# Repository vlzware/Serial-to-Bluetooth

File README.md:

# RS485 to Bluetooth Hardware Interface

- Connect a RS485 serial interface to a Bluetooth device (like a smartphone);
- Fully programmable function thanks to an ATMEGA microcontroller, easily accessible through 6-pin header;
- Industrial-grade components with lot of redundancy;
- Originally developed as the hardware companion for my [BTDisplay - controlling a Siemens wind turbine with my smartphone](https://github.com/holodon/BTDisplayOSS);
- General purpose LED;
- Rechargeable battery with a simple but effective charging circuit;
- Really small form factor - pictures available in the [media section](media).

## Legal
- Open-source hardware, released under [MIT](LICENSE) license;
- Layout and schematics build with [EAGLE CAD](https://www.autodesk.com/products/eagle/overview).

## 
<p style="text-align: right">
    <a href="https://vlzware.com">Vladimir Zhelezarov</a> © 2017
</p>

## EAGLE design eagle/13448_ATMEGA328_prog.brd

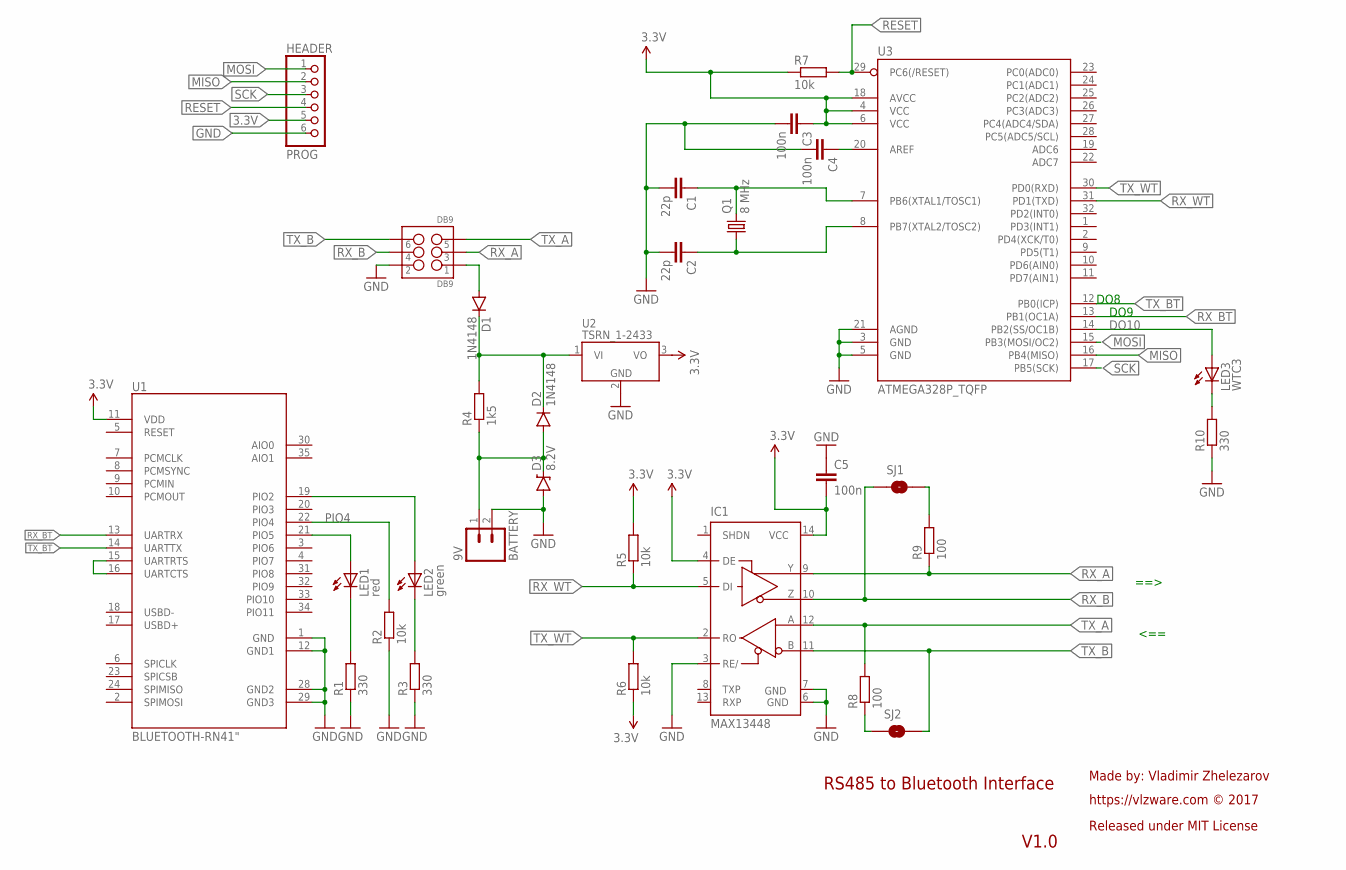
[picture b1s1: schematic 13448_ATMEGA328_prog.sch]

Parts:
BATTERY: 9V; 1X02_LOCK
C1, C2: 22p; 1206
C3, C4, C5: 100n; 1206
D1, D2: 1N4148; DIODE-1N4148
D3: 8.2V; DIODE-BZT52
DB9: DB9; 2X3
HEADER: PROG; 1X06
IC1: MAX13448; SO14
LED1: red; LED3MM
LED2: green; LED3MM
LED3: WTC3; LED3MM
Q1: 8 MHz; HC49UP
R1, R3, R10: 330; M1206
R2, R5, R6, R7: 10k; M1206
R4: 1k5; 0204V
R8, R9: 100; M1206
SJ1, SJ2: SOLDERJUMPERNC; SJ_2S
U1: BLUETOOTH-RN41"; RN41
U2: TSRN_1-2433; TSR-1
U3: ATMEGA328P_TQFP; TQFP32-08

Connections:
3.3V: C3.1, C5.2, HEADER.5, IC1.4 (DE), IC1.14 (VCC), R5.2, R6.1, R7.1, U1.11 (VDD), U2.3 (VO), U3.4 (VCC), U3.6 (VCC), U3.18 (AVCC)
24V: D1.A, DB9.1
D1: LED1.K (C), R1.2
D2: LED2.K (C), R3.2
DO10: LED3.A, U3.14 (PB2(SS/OC1B))
GND: BATTERY.2, C1.2, C2.2, C3.2, C4.2, C5.1, D3.A, DB9.2, HEADER.6, IC1.3 (RE/), IC1.6 (GND), IC1.7 (GND), R1.1, R2.1, R3.1, R10.1, U1.1 (GND), U1.12 (GND1), U1.28 (GND2), U1.29 (GND3), U2.2 (GND), U3.3 (GND), U3.5 (GND), U3.21 (AGND)
MISO: HEADER.2, U3.16 (PB4(MISO))
MOSI: HEADER.1, U3.15 (PB3(MOSI/OC2))
unnamed: LED1.A, U1.21 (PIO5)
unnamed: LED2.A, U1.19 (PIO2)
unnamed: U1.15 (UARTRTS), U1.16 (UARTCTS)
unnamed: LED3.K (C), R10.2
unnamed: R8.1, SJ2.1
unnamed: R9.2, SJ1.2
unnamed: BATTERY.1, D2.A, D3.C, R4.1
unnamed: C4.1, U3.20 (AREF)
unnamed: C1.1, Q1.2, U3.7 (PB6(XTAL1/TOSC1))
unnamed: C2.1, Q1.1, U3.8 (PB7(XTAL2/TOSC2))
PIO4: R2.2, U1.22 (PIO4)
RESET: HEADER.4, R7.2, U3.29 (PC6(/RESET))
RX_A: DB9.3, IC1.9 (Y), R9.1
RX_B: DB9.4, IC1.10 (Z), SJ1.1
RX_BT: U1.13 (UARTRX), U3.13 (PB1(OC1A))
RX_WT: IC1.5 (DI), R5.1, U3.31 (PD1(TXD))
SCK: HEADER.3, U3.17 (PB5(SCK))
TX_A: DB9.5, IC1.12 (A), R8.2
TX_B: DB9.6, IC1.11 (B), SJ2.2
TX_BT: U1.14 (UARTTX), U3.12 (PB0(ICP))
TX_WT: IC1.2 (RO), R6.2, U3.30 (PD0(RXD))
VI: D1.C, D2.C, R4.2, U2.1 (VI)

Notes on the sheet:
==>
<==
DO8
DO9
RS485 to Bluetooth Interface
Made by: Vladimir Zhelezarov
Released under MIT License
https://vlzware.com © 2017
V1.0

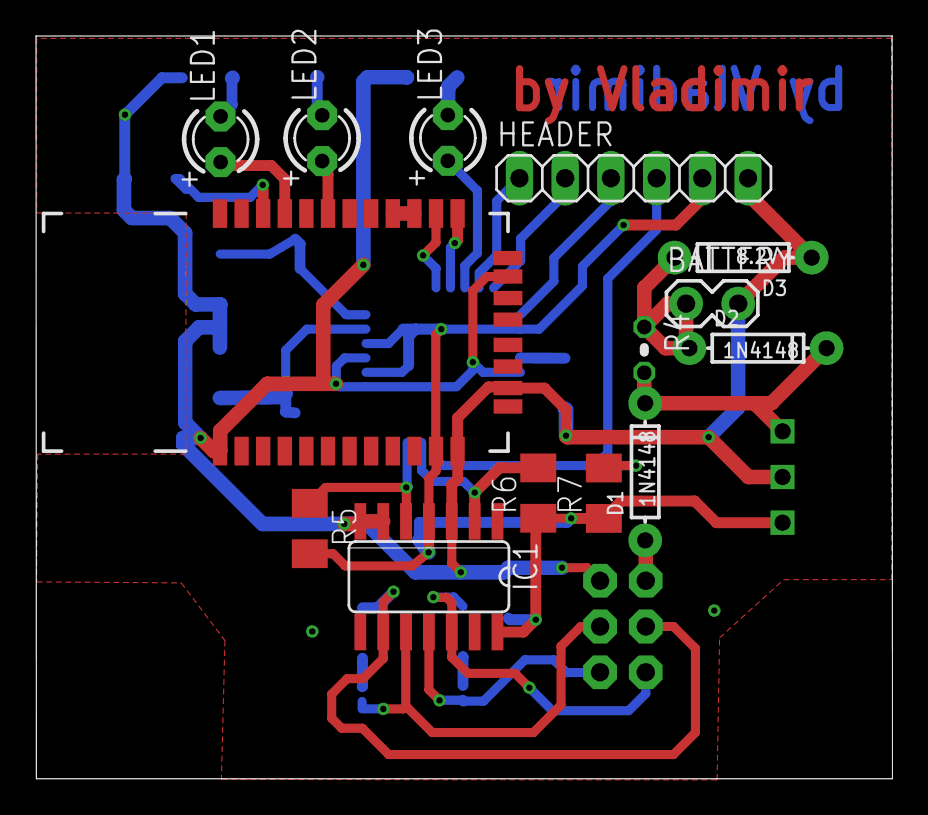
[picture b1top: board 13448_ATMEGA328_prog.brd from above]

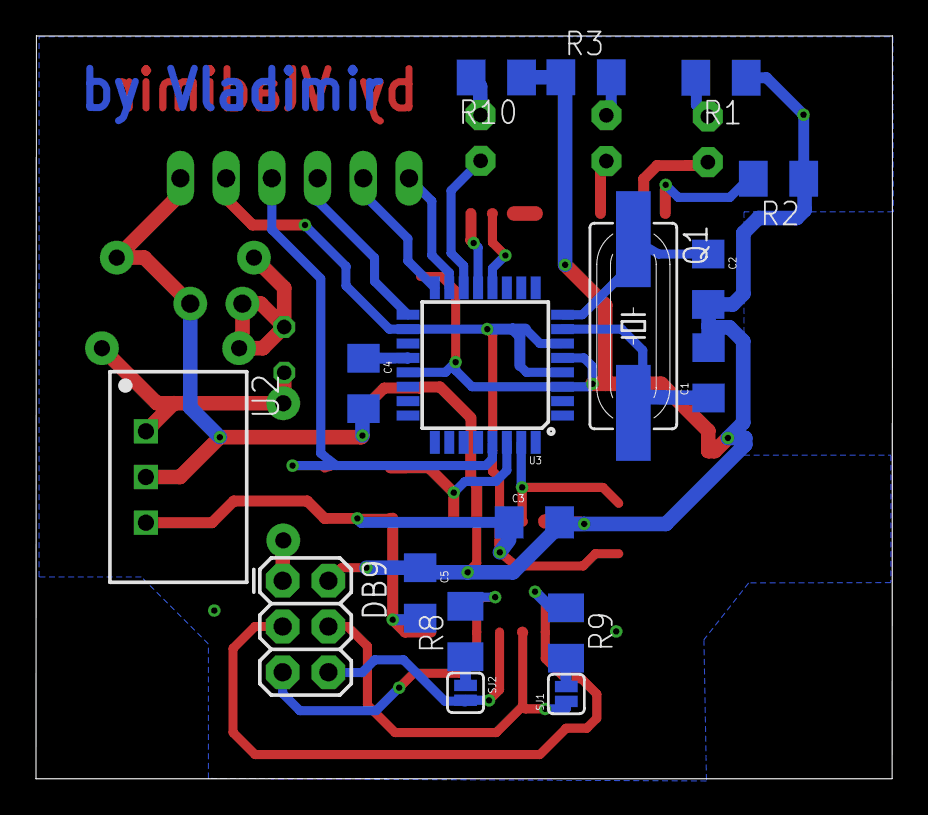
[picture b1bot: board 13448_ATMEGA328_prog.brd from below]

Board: 2 copper layers, 47.6 x 41.3 mm, 31 parts (17 on the bottom side), 30 nets.

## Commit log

2017-10-17 new pics

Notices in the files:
parts and their libraries:
SparkFun-Connectors: Licensing: Creative Commons ShareAlike 4.0 International - https://creativecommons.org/licenses/by-sa/4.0
